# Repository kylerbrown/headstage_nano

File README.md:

# HeadstageNano2

A small Intan RHD2000 amplifier PCB. Design is almost identical to one recievied from Hamish Mehaffey, with the addition of working impedance checks.

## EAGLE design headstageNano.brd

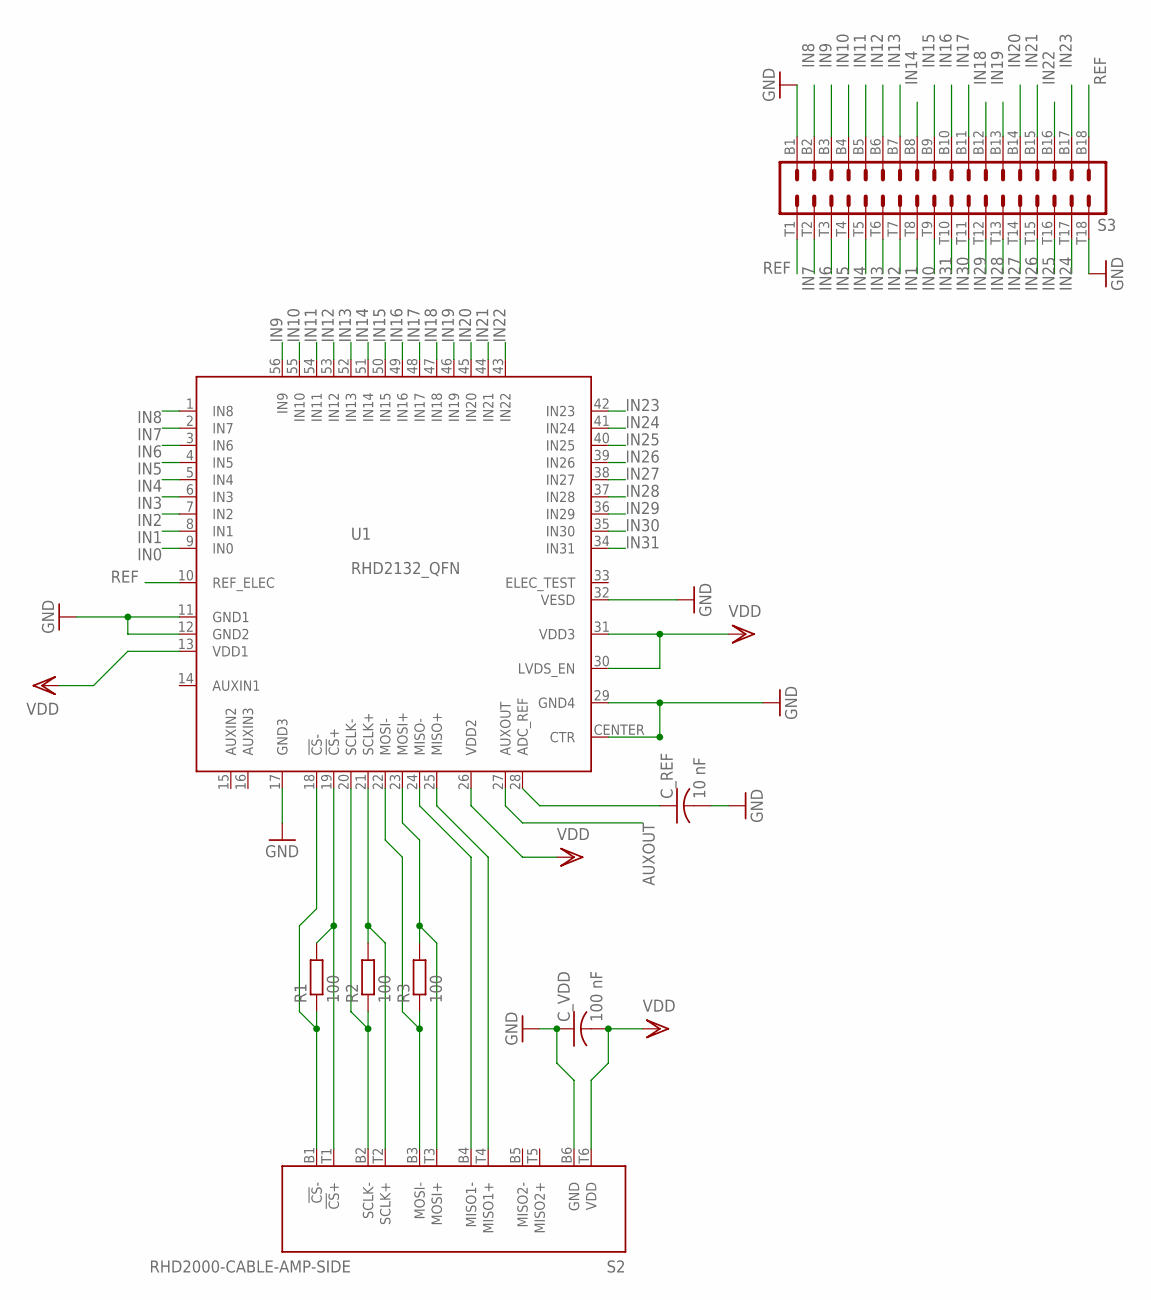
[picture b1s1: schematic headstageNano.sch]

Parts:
C_REF: 10 nF; C0402K
C_VDD: 100 nF; C0402K
R1, R2, R3: 100; R0402
S2: RHD2000-CABLE-AMP-SIDE; OMNETICS_PZN-12-AA
S3: OMNETICS_A79025
U1: RHD2132_QFN; QFN56_8_X_8_LARGE

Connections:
ADC_REF: C_REF.1, U1.28 (ADC_REF)
AUXOUT: U1.27 (AUXOUT)
CS+: R1.2, S2.T1 (!CS!+), U1.19 (!CS!+)
CS-: R1.1, S2.B1 (!CS!-), U1.18 (!CS!-)
GND: C_REF.2, C_VDD.1, S2.B6 (GND), S3.B1, S3.T18, U1.11 (GND1), U1.12 (GND2), U1.17 (GND3), U1.29 (GND4), U1.32 (VESD), U1.CENTER (CTR)
IN0: S3.T9, U1.9 (IN0)
IN1: S3.T8, U1.8 (IN1)
IN2: S3.T7, U1.7 (IN2)
IN3: S3.T6, U1.6 (IN3)
IN4: S3.T5, U1.5 (IN4)
IN5: S3.T4, U1.4 (IN5)
IN6: S3.T3, U1.3 (IN6)
IN7: S3.T2, U1.2 (IN7)
IN8: S3.B2, U1.1 (IN8)
IN9: S3.B3, U1.56 (IN9)
IN10: S3.B4, U1.55 (IN10)
IN11: S3.B5, U1.54 (IN11)
IN12: S3.B6, U1.53 (IN12)
IN13: S3.B7, U1.52 (IN13)
IN14: S3.B8, U1.51 (IN14)
IN15: S3.B9, U1.50 (IN15)
IN16: S3.B10, U1.49 (IN16)
IN17: S3.B11, U1.48 (IN17)
IN18: S3.B12, U1.47 (IN18)
IN19: S3.B13, U1.46 (IN19)
IN20: S3.B14, U1.45 (IN20)
IN21: S3.B15, U1.44 (IN21)
IN22: S3.B16, U1.43 (IN22)
IN23: S3.B17, U1.42 (IN23)
IN24: S3.T17, U1.41 (IN24)
IN25: S3.T16, U1.40 (IN25)
IN26: S3.T15, U1.39 (IN26)
IN27: S3.T14, U1.38 (IN27)
IN28: S3.T13, U1.37 (IN28)
IN29: S3.T12, U1.36 (IN29)
IN30: S3.T11, U1.35 (IN30)
IN31: S3.T10, U1.34 (IN31)
MISO1+: S2.T4 (MISO1+), U1.25 (MISO+)
MISO1-: S2.B4 (MISO1-), U1.24 (MISO-)
MOSI+: R3.2, S2.T3 (MOSI+), U1.23 (MOSI+)
MOSI-: R3.1, S2.B3 (MOSI-), U1.22 (MOSI-)
REF: S3.B18, S3.T1, U1.10 (REF_ELEC)
SCLK+: R2.2, S2.T2 (SCLK+), U1.21 (SCLK+)
SCLK-: R2.1, S2.B2 (SCLK-), U1.20 (SCLK-)
VDD: C_VDD.2, S2.T6 (VDD), U1.13 (VDD1), U1.26 (VDD2), U1.30 (LVDS_EN), U1.31 (VDD3)

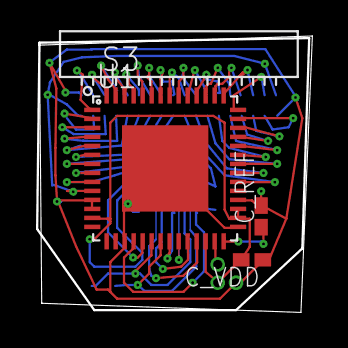
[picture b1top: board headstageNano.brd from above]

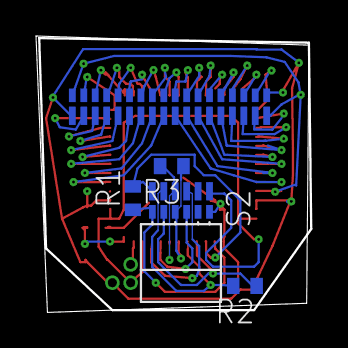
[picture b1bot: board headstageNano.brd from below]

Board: 2 copper layers, 15.2 x 15.2 mm, 8 parts (4 on the bottom side), 44 nets.

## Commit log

2015-09-28 ungrounded pin 33 elec_test for impedance tests
2015-09-28 Rename README.txt to README.md
2015-09-29 adding a connection diagram pdf and a parts list
2015-10-08 updating capacitor values
